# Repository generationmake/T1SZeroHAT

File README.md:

# T1SZeroHAT
Raspberry Pi HAT with Microchip LAN8651 T1S controller

## PCB

### Top

### Bottom

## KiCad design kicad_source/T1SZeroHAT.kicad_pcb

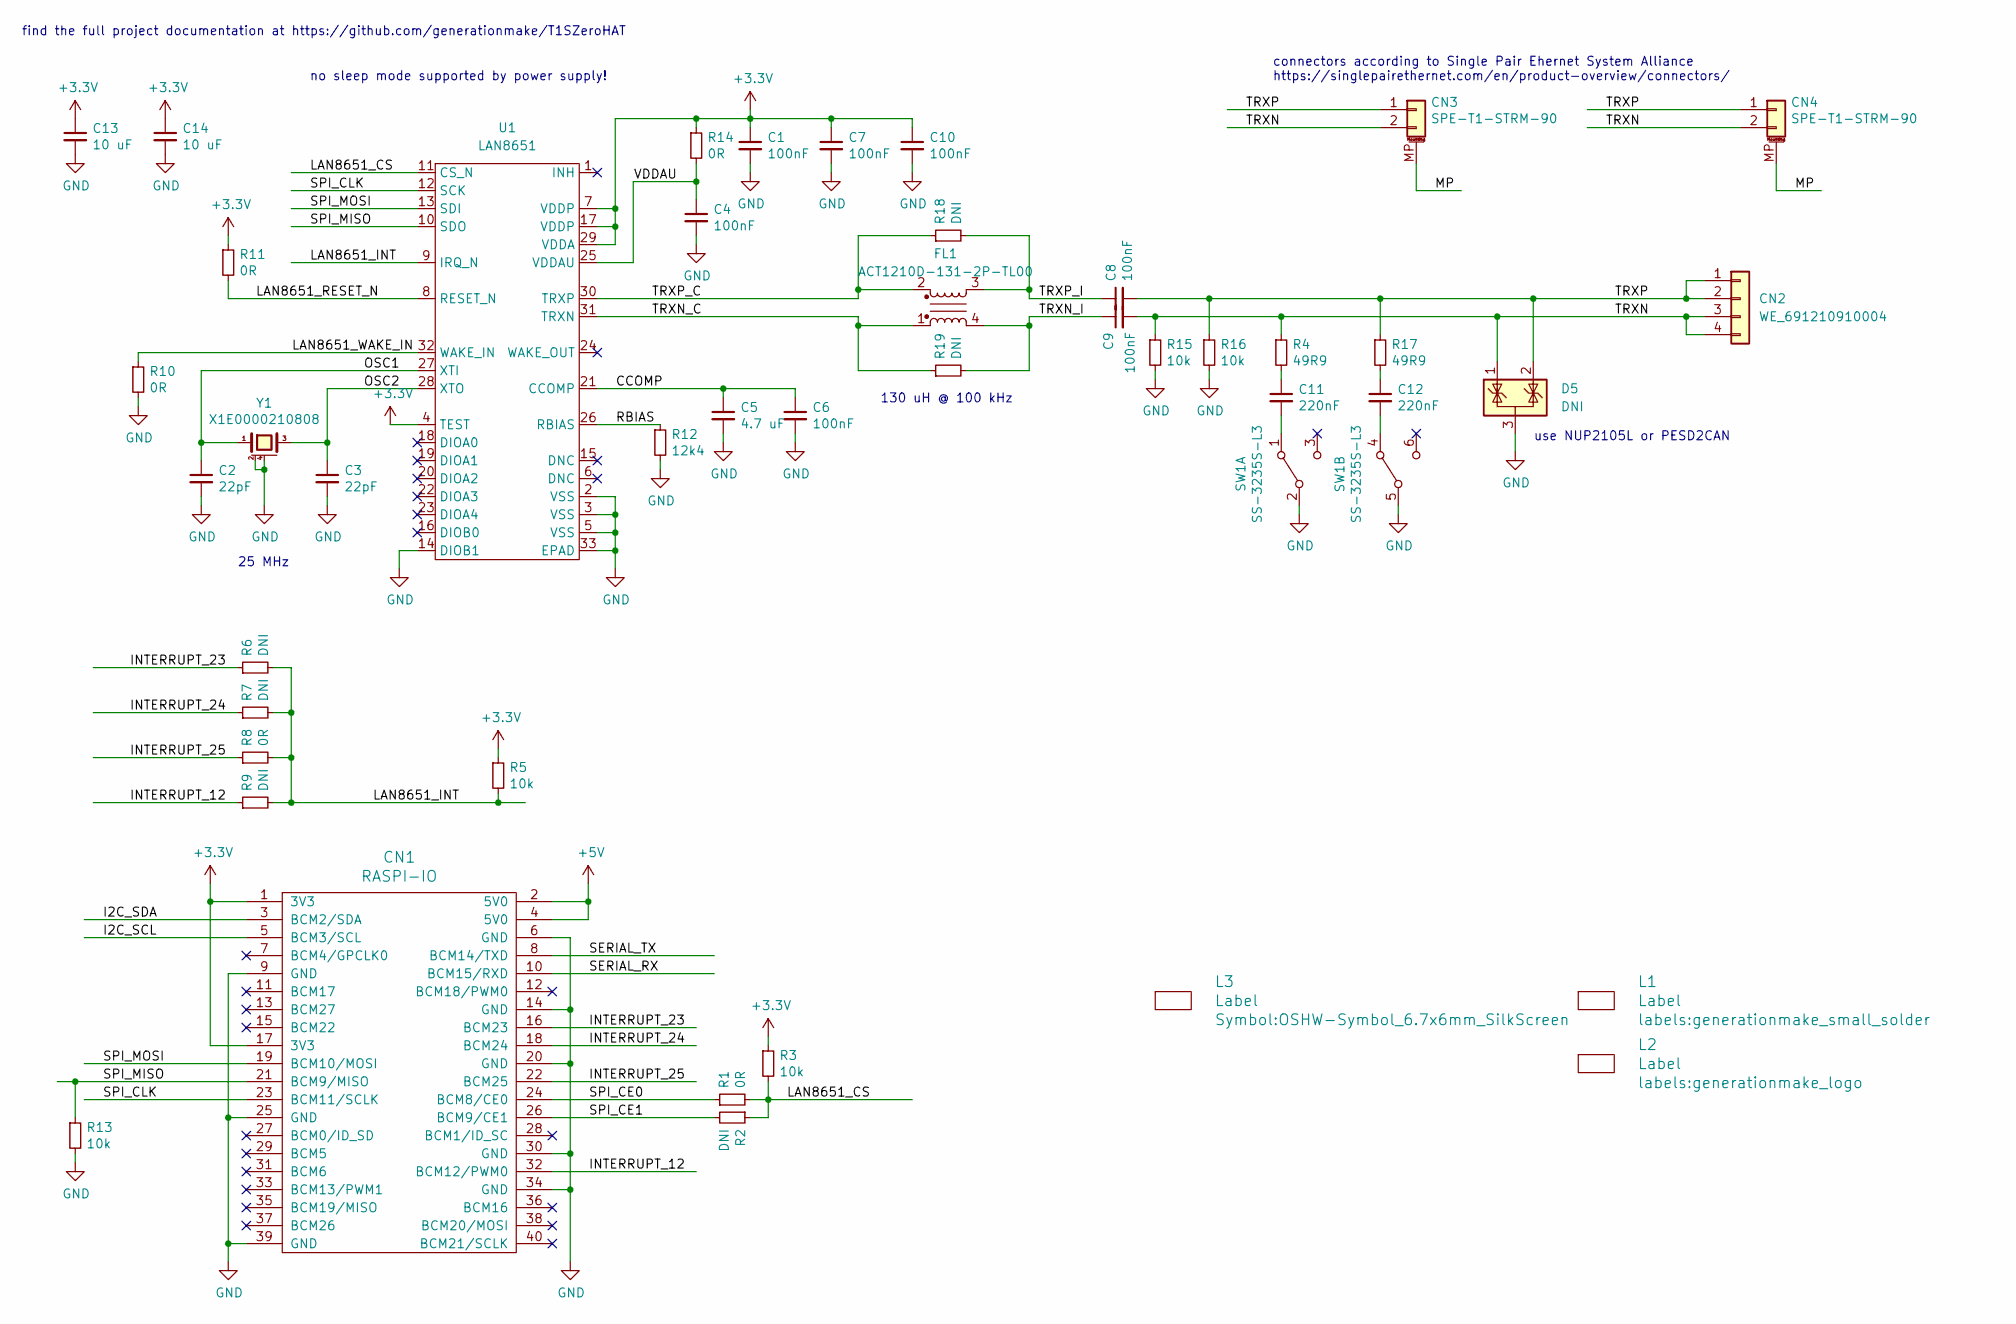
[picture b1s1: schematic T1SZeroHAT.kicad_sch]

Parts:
C1, C4, C6, C7, C8, C9, C10: 100nF; C_0603_1608Metric; LCSC C14663
C2, C3: 22pF; C_0603_1608Metric
C5: 4.7 uF; C_0603_1608Metric
C11, C12: 220nF; C_0603_1608Metric
C13, C14: 10 uF; C_0603_1608Metric
CN1: RASPI-IO; RASPI_ZERO_HAT_EDGE; LCSC C50982
CN2: WE_691210910004
CN3, CN4: SPE-T1-STRM-90
D5: DNI; SOT-23
FL1: ACT1210D-131-2P-TL00; TDK_ACT1210D
L1: Label; generationmake_small_solder
L2: Label; generationmake_logo
L3: Label; OSHW-Symbol_6.7x6mm_SilkScreen
R1, R8, R10, R11, R14: 0R; R_0603_1608Metric; LCSC C2889381
R2, R6, R7, R9, R18, R19: DNI; R_0603_1608Metric
R3, R5, R13: 10k; R_0603_1608Metric; LCSC C25804
R4, R17: 49R9; R_1206_3216Metric
R12: 12k4; R_0603_1608Metric
R15, R16: 10k; R_1206_3216Metric; LCSC C25804
SW1: SS-3235S-L3; SW_DPDT_XKB_SS-3235S-L3; LCSC C381098
U1: LAN8651; QFN-32-1EP_5x5mm_P0.5mm_EP3.45x3.45mm
Y1: X1E0000210808; Crystal_SMD_3225-4Pin_3.2x2.5mm; LCSC C255941

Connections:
+3.3V: C1.1, C7.1, C10.1, C13.1, C14.1, CN1.1 (3V3), CN1.17 (3V3), R3.1, R5.1, R11.1, R14.1, U1.4 (TEST), U1.7 (VDDP), U1.17 (VDDP), U1.29 (VDDA)
+5V: CN1.2 (5V0), CN1.4 (5V0)
/CCOMP: C5.1, C6.1, U1.21 (CCOMP)
/I2C_SCL: CN1.5 (BCM3/SCL)
/I2C_SDA: CN1.3 (BCM2/SDA)
/INTERRUPT_12: CN1.32 (BCM12/PWM0), R9.1
/INTERRUPT_23: CN1.16 (BCM23), R6.1
/INTERRUPT_24: CN1.18 (BCM24), R7.1
/INTERRUPT_25: CN1.22 (BCM25), R8.1
/LAN8651_CS: R1.2, R2.1, R3.2, U1.11 (CS_N)
/LAN8651_INT: R5.2, R6.2, R7.2, R8.2, R9.2, U1.9 (IRQ_N)
/LAN8651_RESET_N: R11.2, U1.8 (RESET_N)
/LAN8651_WAKE_IN: R10.1, U1.32 (WAKE_IN)
/MP: CN3.MP (MountPin), CN4.MP (MountPin)
/OSC1: C2.1, U1.27 (XTI), Y1.1
/OSC2: C3.1, U1.28 (XTO), Y1.3
/RBIAS: R12.1, U1.26 (RBIAS)
/SERIAL_RX: CN1.10 (BCM15/RXD)
/SERIAL_TX: CN1.8 (BCM14/TXD)
/SPI_CE0: CN1.24 (BCM8/CE0), R1.1
/SPI_CE1: CN1.26 (BCM9/CE1), R2.2
/SPI_CLK: CN1.23 (BCM11/SCLK), U1.12 (SCK)
/SPI_MISO: CN1.21 (BCM9/MISO), R13.1, U1.10 (SDO)
/SPI_MOSI: CN1.19 (BCM10/MOSI), U1.13 (SDI)
/TRXN: C9.2, CN2.3, CN2.4, CN3.2, CN4.2, D5.1 (K), R4.1, R15.1
/TRXN_C: FL1.1, R19.1, U1.31 (TRXN)
/TRXN_I: C9.1, FL1.4, R19.2
/TRXP: C8.2, CN2.1, CN2.2, CN3.1, CN4.1, D5.2 (K), R16.1, R17.1
/TRXP_C: FL1.2, R18.1, U1.30 (TRXP)
/TRXP_I: C8.1, FL1.3, R18.2
/VDDAU: C4.1, R14.2, U1.25 (VDDAU)
GND: C1.2, C2.2, C3.2, C4.2, C5.2, C6.2, C7.2, C10.2, C13.2, C14.2, CN1.6 (GND), CN1.9 (GND), CN1.14 (GND), CN1.20 (GND), CN1.25 (GND), CN1.30 (GND), CN1.34 (GND), CN1.39 (GND), D5.3 (A), R10.2, R12.2, R13.2, R15.2, R16.2, SW1.2 (B), SW1.5 (B), U1.2 (VSS), U1.3 (VSS), U1.5 (VSS), U1.14 (DIOB1), U1.33 (EPAD), Y1.2 (case), Y1.4 (case)
unnamed: C11.1, R4.2
unnamed: C12.1, R17.2
unnamed: C11.2, SW1.1 (A)
unnamed: C12.2, SW1.4 (A)

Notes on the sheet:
130 uH @ 100 kHz
find the full project documentation at https://github.com/generationmake/T1SZeroHAT
connectors according to Single Pair Ehernet System Alliance https://singlepairethernet.com/en/product-overview/connectors/
use NUP2105L or PESD2CAN
no sleep mode supported by power supply!
25 MHz

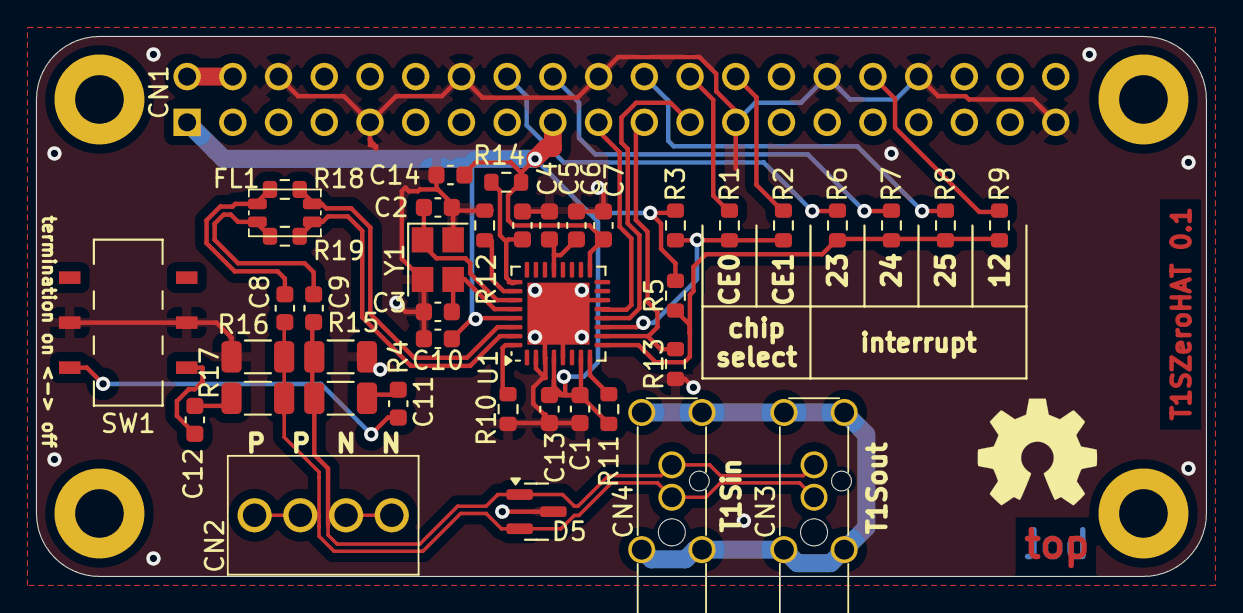
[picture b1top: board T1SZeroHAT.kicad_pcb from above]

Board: 2 copper layers, 65.0 x 30.0 mm, 45 parts (1 on the bottom side), 32 nets.

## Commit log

2023-08-27 added kicad project
2023-08-27 added LAN8651 to the schematic
2023-08-27 added pdf schematic
2023-08-30 added common mode choke on ethernet lines
2023-08-31 made first draft of layout
2023-08-31 added images
2023-09-12 updated schematic for power delivery
2023-09-12 updated layout for power delivery
2025-02-16 updated to kicad version 8
2025-02-23 removed power delivery parts since they are not specified
2025-02-23 changed R14..R17 to 1206 according to microchip reference schematic
2025-02-23 connected DIOB1 directly to GND as recommended in datasheet
2025-02-23 reworked power part
2025-02-23 corrected common mode choke and added part number
2025-02-23 updated schematic pdf
2025-02-23 updated images
2025-02-23 fixed some DRCs

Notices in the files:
kicad_source/T1SZeroHAT.kicad_pcb:
Licensed under CERN-OHL-W v2
